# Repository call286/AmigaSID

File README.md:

# AmigaSID Zorro II card

Board Render Front           |  Board Render Back
:-------------------------:|:-------------------------:
 | 

[Schematic PDF](Hardware/AmigaSID-schematic.pdf)

Forked from https://github.com/Sgw32/AmigaSID which forked from http://www.amibay.com/showthread.php?108629-Amiga-SID-player-for-Zorro-slot

Can't find the original thread on Amibay sadly, so i can't do full credits here.

## Changes

- Changed most of the components to SMD, major rerouting.
- Added 100k pull down resistor and 470pF capacitor to EXT_IN of SID like pointed out at the original schematics.
- Added 245 buffer to D0-D7 databus lines.
- Changed crystal to 7050 part.
- Tied Amiga /RST to RST of SID via solderjumper (default connected)
  - can be removed with a cut and be used at A4k with it's power LED connected to H1
- Added 8 jumpers (JP2-JP9) to set the memory address the SID can be accessed from the player side (needs patched player to use that address)
- Added filter caps to vcc lines of the IC's
- Changed audio connector to a more common type
- Moved filter caps closer to IC's
- Added logo
- Floating 74LS00 inputs tied to VCC
- Flipped polarity on C10 (SID_AUDIO_IN)
- Added jumper to disconnect audio out cap from output pins
  - instead you now can fit a little amp board like shown Gadgets video about the original version of the card
  - also added one GND and one 12V pin for powering the amp

Thanks to [LIV2](https://github.com/LIV2) and [GadgetUK](https://www.youtube.com/channel/UCRBWJ9JeJ3Q8ssn_ibii-Cg) for the help in this project.

Use at your own risk!!!
~~As of now (06.01.2021) i haven't tested that, not even ordered boards!~~
Boards were kindly provided by SparxUK - Thanks mate!
The boards worked fine on my A500 with a Zorro2 adapter and a NanoSwinSID.

## Jumper setting

The bank of jumpers on top of the card (JP2-JP9) is used to set the memory address used by the card and the players.

Jumper setting for EE range:

| Jumper  |   Setting    |
| :------:|:-----------: |
| JP2     |  1-2 (LOW)   |
| JP3     |  2-3 (HIGH)  |
| JP4     |  2-3 (HIGH)  |
| JP5     |  2-3 (HIGH)  |
| JP6     |  1-2 (LOW)   |
| JP7     |  2-3 (HIGH)  |
| JP8     |  2-3 (HIGH)  |
| JP9     |  2-3 (HIGH)  |

## Folder: Hardware

Here you'll find the KiCAD6 project for the board.
Also there is a HTML BOM for parts placement and a jlcpcb folder with gerbers and BOM/POS for assembly (only the SMD caps/resistors, no ic's or THT parts!)

## Folder: Software

Here you'll find patched versions of players to use on the Amiga.

## TODO
- Add more/better documentation
- ~~Test the Hardware, order boards~~
  - Boards were kindly provided by SparxUK

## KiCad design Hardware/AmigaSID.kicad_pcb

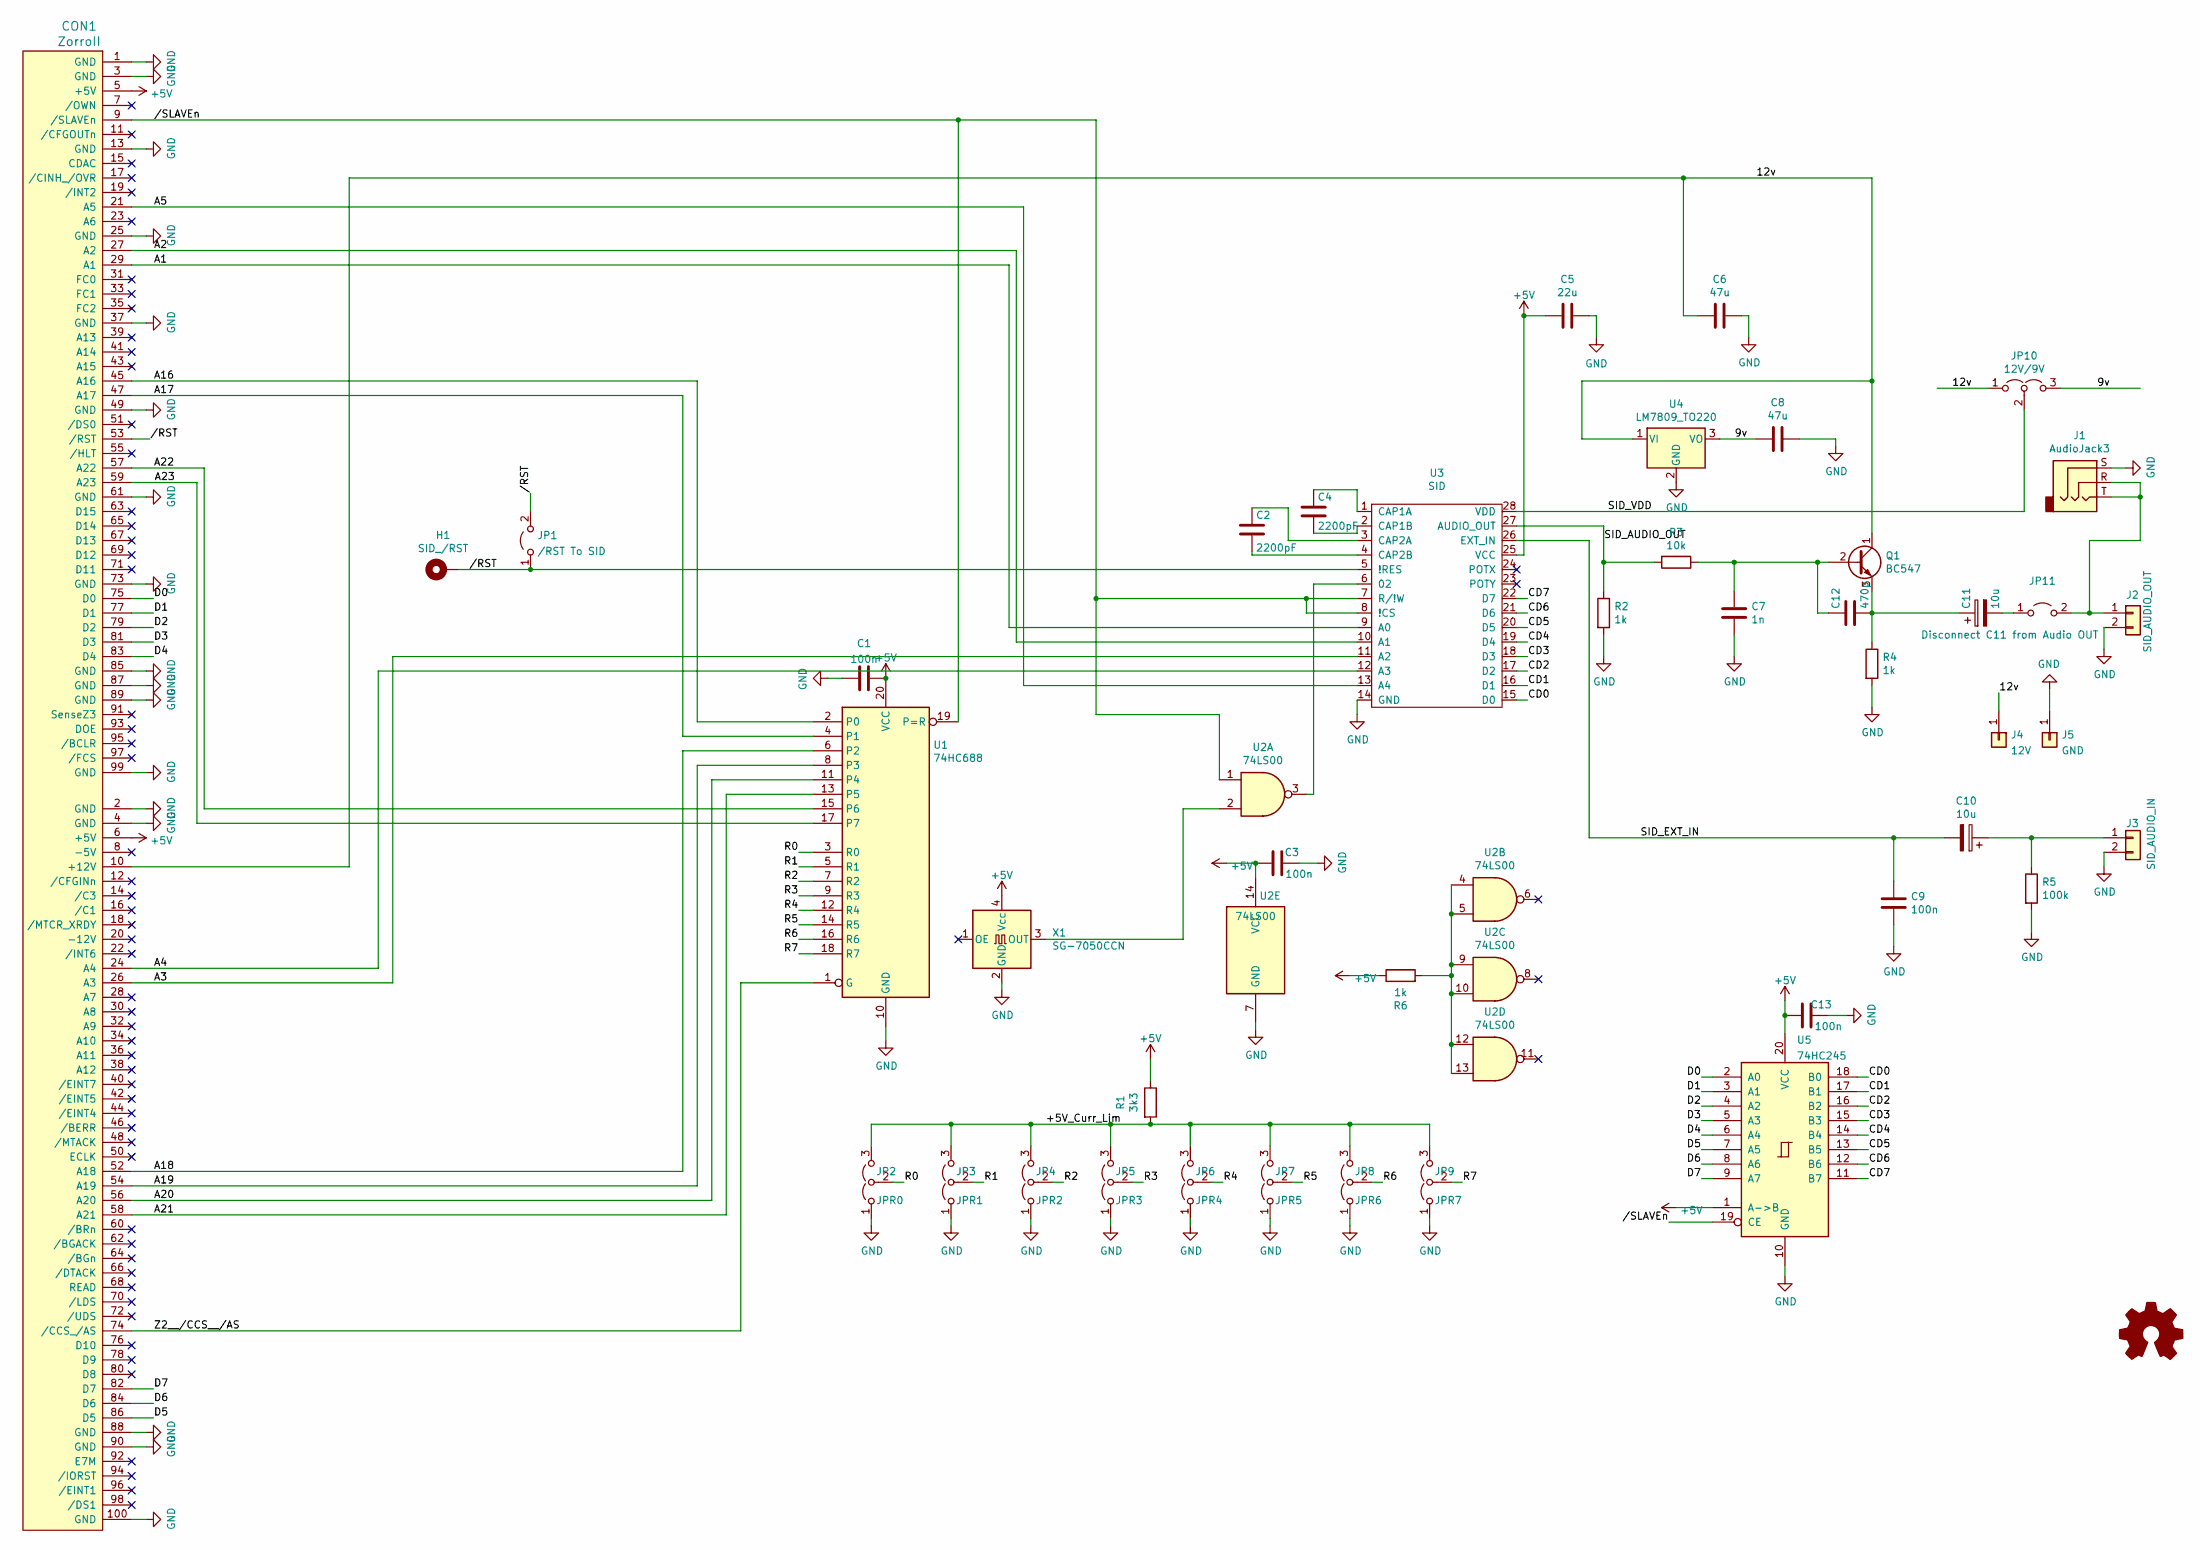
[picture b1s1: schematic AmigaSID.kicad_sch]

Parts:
C1, C3, C9, C13: 100n; C_0805_2012Metric_Pad1.18x1.45mm_HandSolder
C2, C4: 2200pF; C_0805_2012Metric_Pad1.18x1.45mm_HandSolder
C5: 22u; C_0805_2012Metric_Pad1.18x1.45mm_HandSolder
C6, C8: 47u; C_0805_2012Metric_Pad1.18x1.45mm_HandSolder
C7: 1n; C_0805_2012Metric_Pad1.18x1.45mm_HandSolder
C10, C11: 10u; CP_Radial_D7.5mm_P2.50mm
C12: 470p; C_0805_2012Metric_Pad1.18x1.45mm_HandSolder
CON1: ZorroII
H1: SID_/RST; PinHeader_1x01_P2.54mm_Vertical
J1: AudioJack3; Jack_3.5mm_4UCON
J2: SID_AUDIO_OUT; TerminalBlock_4Ucon_1x02_P3.50mm_Horizontal
J3: SID_AUDIO_IN; TerminalBlock_4Ucon_1x02_P3.50mm_Horizontal
J4: 12V; PinHeader_1x01_P2.54mm_Vertical
J5: GND; PinHeader_1x01_P2.54mm_Vertical
JP1: /RST To SID; SolderJumper-2_P1.3mm_Bridged_RoundedPad1.0x1.5mm
JP2: JPR0; PinHeader_1x03_P2.54mm_Vertical
JP3: JPR1; PinHeader_1x03_P2.54mm_Vertical
JP4: JPR2; PinHeader_1x03_P2.54mm_Vertical
JP5: JPR3; PinHeader_1x03_P2.54mm_Vertical
JP6: JPR4; PinHeader_1x03_P2.54mm_Vertical
JP7: JPR5; PinHeader_1x03_P2.54mm_Vertical
JP8: JPR6; PinHeader_1x03_P2.54mm_Vertical
JP9: JPR7; PinHeader_1x03_P2.54mm_Vertical
JP10: 12V/9V; PinHeader_1x03_P2.54mm_Horizontal
JP11: Disconnect C11 from Audio OUT; PinHeader_1x02_P2.54mm_Vertical
Q1: BC547; TO-92_Inline_Wide
R1: 3k3; R_0805_2012Metric_Pad1.20x1.40mm_HandSolder
R2, R4, R6: 1k; R_0805_2012Metric_Pad1.20x1.40mm_HandSolder
R3: 10k; R_0805_2012Metric_Pad1.20x1.40mm_HandSolder
R5: 100k; R_0805_2012Metric_Pad1.20x1.40mm_HandSolder
U1: 74HC688; TSSOP-20_4.4x6.5mm_P0.65mm
U2: 74LS00; SOIC-14_3.9x8.7mm_P1.27mm
U3: SID; DIP-28_W15.24mm_Socket_LongPads
U4: LM7809_TO220; TO-220-3_Horizontal_TabDown
U5: 74HC245; SOIC-20W_7.5x12.8mm_P1.27mm
X1: SG-7050CCN; Oscillator_SMD_SeikoEpson_SG8002CA-4Pin_7.0x5.0mm

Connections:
+5V: C1.1, C3.1, C5.2, C13.1, CON1.5 (+5V), CON1.6 (+5V), R1.1, R6.1, U1.20 (VCC), U2.14 (VCC), U3.25 (VCC), U5.1 (A->B), U5.20 (VCC), X1.4 (Vcc)
/9v: C8.2, JP10.3 (B), U4.3 (VO)
/12v: C6.2, CON1.10 (+12V), J4.1, JP10.1 (A), Q1.1 (C), U4.1 (VI)
/+5V_Curr_Lim: JP2.3 (B), JP3.3 (B), JP4.3 (B), JP5.3 (B), JP6.3 (B), JP7.3 (B), JP8.3 (B), JP9.3 (B), R1.2
/A1: CON1.29 (A1), U3.9 (A0)
/A2: CON1.27 (A2), U3.10 (A1)
/A3: CON1.26 (A3), U3.11 (A2)
/A4: CON1.24 (A4), U3.12 (A3)
/A5: CON1.21 (A5), U3.13 (A4)
/A16: CON1.45 (A16), U1.2 (P0)
/A17: CON1.47 (A17), U1.4 (P1)
/A18: CON1.52 (A18), U1.6 (P2)
/A19: CON1.54 (A19), U1.8 (P3)
/A20: CON1.56 (A20), U1.11 (P4)
/A21: CON1.58 (A21), U1.13 (P5)
/A22: CON1.57 (A22), U1.15 (P6)
/A23: CON1.59 (A23), U1.17 (P7)
/CD0: U3.15 (D0), U5.18 (B0)
/CD1: U3.16 (D1), U5.17 (B1)
/CD2: U3.17 (D2), U5.16 (B2)
/CD3: U3.18 (D3), U5.15 (B3)
/CD4: U3.19 (D4), U5.14 (B4)
/CD5: U3.20 (D5), U5.13 (B5)
/CD6: U3.21 (D6), U5.12 (B6)
/CD7: U3.22 (D7), U5.11 (B7)
/D0: CON1.75 (D0), U5.2 (A0)
/D1: CON1.77 (D1), U5.3 (A1)
/D2: CON1.79 (D2), U5.4 (A2)
/D3: CON1.81 (D3), U5.5 (A3)
/D4: CON1.83 (D4), U5.6 (A4)
/D5: CON1.86 (D5), U5.7 (A5)
/D6: CON1.84 (D6), U5.8 (A6)
/D7: CON1.82 (D7), U5.9 (A7)
/R0: JP2.2 (C), U1.3 (R0)
/R1: JP3.2 (C), U1.5 (R1)
/R2: JP4.2 (C), U1.7 (R2)
/R3: JP5.2 (C), U1.9 (R3)
/R4: JP6.2 (C), U1.12 (R4)
/R5: JP7.2 (C), U1.14 (R5)
/R6: JP8.2 (C), U1.16 (R6)
/R7: JP9.2 (C), U1.18 (R7)
/SID_AUDIO_OUT: R2.1, R3.2, U3.27 (AUDIO_OUT)
/SID_EXT_IN: C9.1, C10.2, U3.26 (EXT_IN)
/SID_VDD: JP10.2 (C), U3.28 (VDD)
/Z2__/CCS__/AS: CON1.74 (/CCS_/AS), U1.1 (G)
//RST: CON1.53 (/RST), H1.1, JP1.1 (A), JP1.2 (B), U3.5 (!RES)
//SLAVEn: CON1.9 (/SLAVEn), U1.19 (P=R), U2.1, U3.7 (R/!W), U3.8 (!CS), U5.19 (CE)
GND: C1.2, C3.2, C5.1, C6.1, C7.2, C8.1, C9.2, C13.2, CON1.1 (GND), CON1.2 (GND), CON1.3 (GND), CON1.4 (GND), CON1.13 (GND), CON1.25 (GND), CON1.37 (GND), CON1.49 (GND), CON1.61 (GND), CON1.73 (GND), CON1.85 (GND), CON1.87 (GND), CON1.88 (GND), CON1.89 (GND), CON1.90 (GND), CON1.99 (GND), CON1.100 (GND), J1.S, J2.2, J3.2, J5.1, JP2.1 (A), JP3.1 (A), JP4.1 (A), JP5.1 (A), JP6.1 (A), JP7.1 (A), JP8.1 (A), JP9.1 (A), R2.2, R4.2, R5.2, U1.10 (GND), U2.7 (GND), U3.14 (GND), U4.2 (GND), U5.10 (GND), X1.2 (GND)
unnamed: C2.1, U3.3 (CAP2A)
unnamed: C2.2, U3.4 (CAP2B)
unnamed: C4.1, U3.1 (CAP1A)
unnamed: C4.2, U3.2 (CAP1B)
unnamed: C10.1, J3.1, R5.1
unnamed: C11.1, C12.2, Q1.3 (E), R4.1
unnamed: C11.2, JP11.1 (A)
unnamed: C7.1, C12.1, Q1.2 (B), R3.1
unnamed: J1.R, J1.T, J2.1, JP11.2 (B)
unnamed: R6.2, U2.4, U2.5, U2.9, U2.10, U2.12, U2.13
unnamed: U2.2, X1.3 (OUT)
unnamed: U2.3, U3.6 (02)

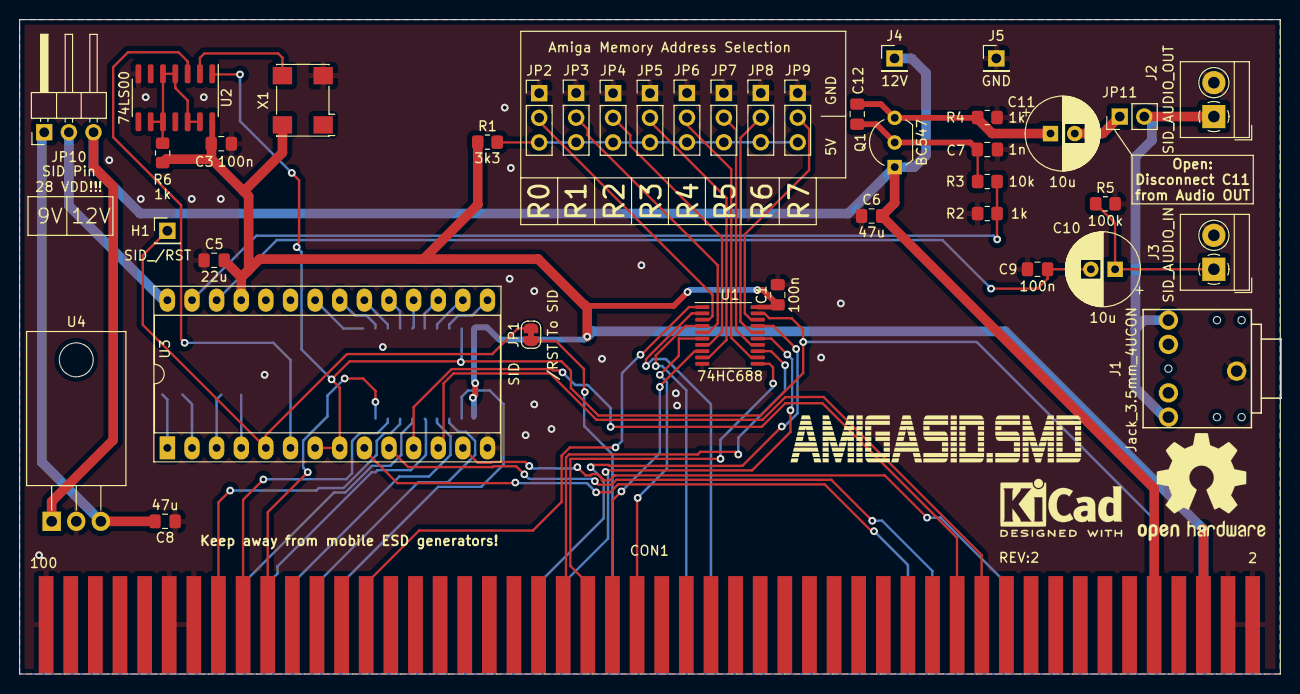
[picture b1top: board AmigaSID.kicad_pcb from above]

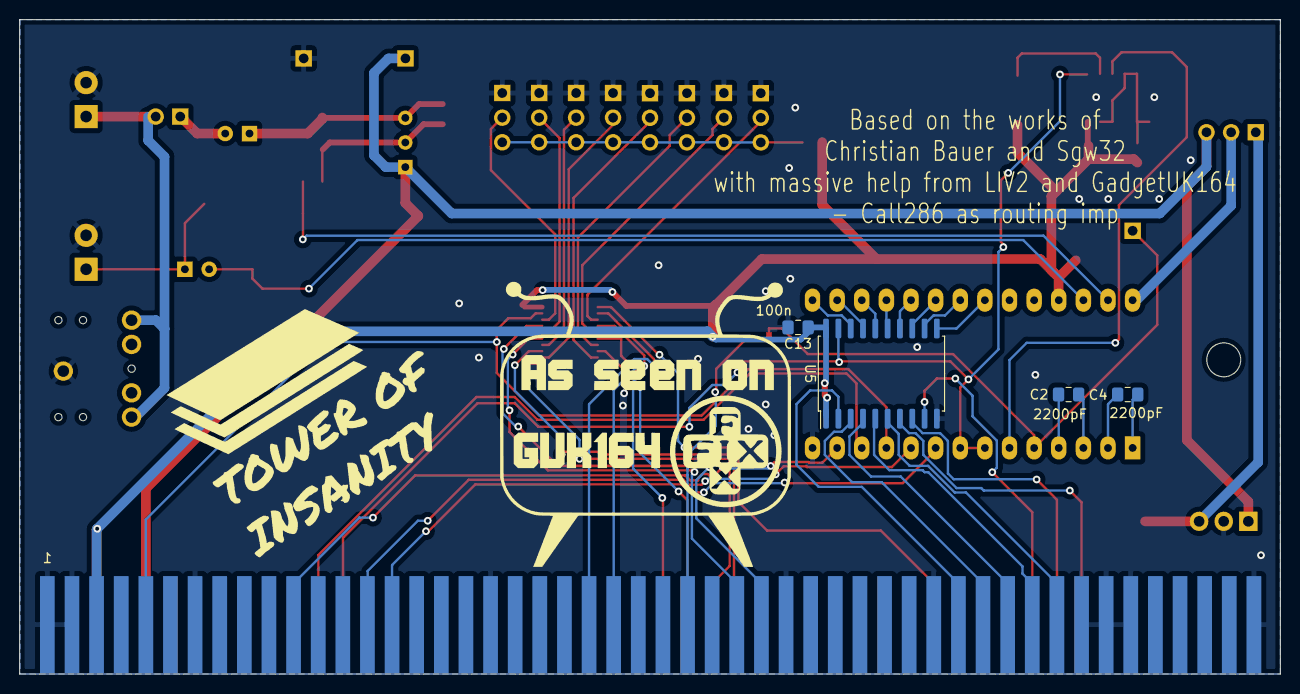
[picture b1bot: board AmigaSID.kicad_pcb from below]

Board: 2 copper layers, 130.0 x 67.5 mm, 44 parts (4 on the bottom side), 60 nets.

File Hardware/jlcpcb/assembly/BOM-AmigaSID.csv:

Comment,Designator,Footprint,LCSC
100k,R5,R_0805_2012Metric_Pad1.20x1.40mm_HandSolder,C17407
10k,R3,R_0805_2012Metric_Pad1.20x1.40mm_HandSolder,C17414
470p,C12,C_0805_2012Metric_Pad1.18x1.45mm_HandSolder,C1743
1k,"R2,R4,R6",R_0805_2012Metric_Pad1.20x1.40mm_HandSolder,C17513
3k3,R1,R_0805_2012Metric_Pad1.20x1.40mm_HandSolder,C26010
2200pF,"C2,C4",C_0805_2012Metric_Pad1.18x1.45mm_HandSolder,C28260
22u,C5,C_0805_2012Metric_Pad1.18x1.45mm_HandSolder,C45783
1n,C7,C_0805_2012Metric_Pad1.18x1.45mm_HandSolder,C46653
100n,"C1,C13,C3,C9",C_0805_2012Metric_Pad1.18x1.45mm_HandSolder,C49678
SID_AUDIO_OUT,J2,TerminalBlock_4Ucon_1x02_P3.50mm_Horizontal,
74LS00,U2,SOIC-14_3.9x8.7mm_P1.27mm,
SID_/RST,H1,PinHeader_1x01_P2.54mm_Vertical,
SID_AUDIO_IN,J3,TerminalBlock_4Ucon_1x02_P3.50mm_Horizontal,
SID,U3,DIP-28_W15.24mm_Socket_LongPads,
10u,C10,CP_Radial_D7.5mm_P2.50mm,
74HC688,U1,TSSOP-20_4.4x6.5mm_P0.65mm,
47u,C6,C_0805_2012Metric_Pad1.18x1.45mm_HandSolder,
BC547,Q1,TO-92_Inline_Wide,
10u,C11,CP_Radial_D7.5mm_P2.50mm,
LM7809_TO220,U4,TO-220-3_Horizontal_TabDown,
AudioJack3,J1,Jack_3.5mm_4UCON,
12V/9V,JP10,PinHeader_1x03_P2.54mm_Horizontal,
47u,C8,C_0805_2012Metric_Pad1.18x1.45mm_HandSolder,
SG-7050CCN,X1,Oscillator_SMD_SeikoEpson_SG8002CA-4Pin_7.0x5.0mm,
JPR3,JP5,PinHeader_1x03_P2.54mm_Vertical,
JPR7,JP9,PinHeader_1x03_P2.54mm_Vertical,
JPR2,JP4,PinHeader_1x03_P2.54mm_Vertical,
/RST To SID,JP1,SolderJumper-2_P1.3mm_Bridged_RoundedPad1.0x1.5mm,
JPR1,JP3,PinHeader_1x03_P2.54mm_Vertical,
JPR4,JP6,PinHeader_1x03_P2.54mm_Vertical,
JPR6,JP8,PinHeader_1x03_P2.54mm_Vertical,
JPR0,JP2,PinHeader_1x03_P2.54mm_Vertical,
12V,J4,PinHeader_1x01_P2.54mm_Vertical,
JPR5,JP7,PinHeader_1x03_P2.54mm_Vertical,
GND,J5,PinHeader_1x01_P2.54mm_Vertical,
Disconnect C11 from Audio OUT,JP11,PinHeader_1x02_P2.54mm_Vertical,
74HC245,U5,SOIC-20W_7.5x12.8mm_P1.27mm,

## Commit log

2022-01-04 * Rev1
    - changed to SMD
    - reroute
    - jumpers for address selection
    - 245 buffer added to D0-D7
    - changed audio connector
    - filter caps
2022-01-04 Add README.md
2022-01-04 - Moved filter caps closer to IC's - Added logo - Floating 245 inputs tied to VCC - Flipped polarity on C10 (SID_AUDIO_IN) - Added jumper to disconnect audio out cap from output pins - instead you no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
2022-01-05 Added Schematic PDF, linked in README.md Added Renders to README.md
2022-01-06 added jlcpcb gerbers/pos/bom, html bom, modified software players updated README.md
2022-01-09 Rev2, moved LDO, reset pin for A4k LED and voltage selection jumper, used only basic parts in JLCPCB bom
